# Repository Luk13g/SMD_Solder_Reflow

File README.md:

# SMD_Solder_Reflow
Soldering system for SMD electronic components on PCBs, adapted in a domestic electric oven

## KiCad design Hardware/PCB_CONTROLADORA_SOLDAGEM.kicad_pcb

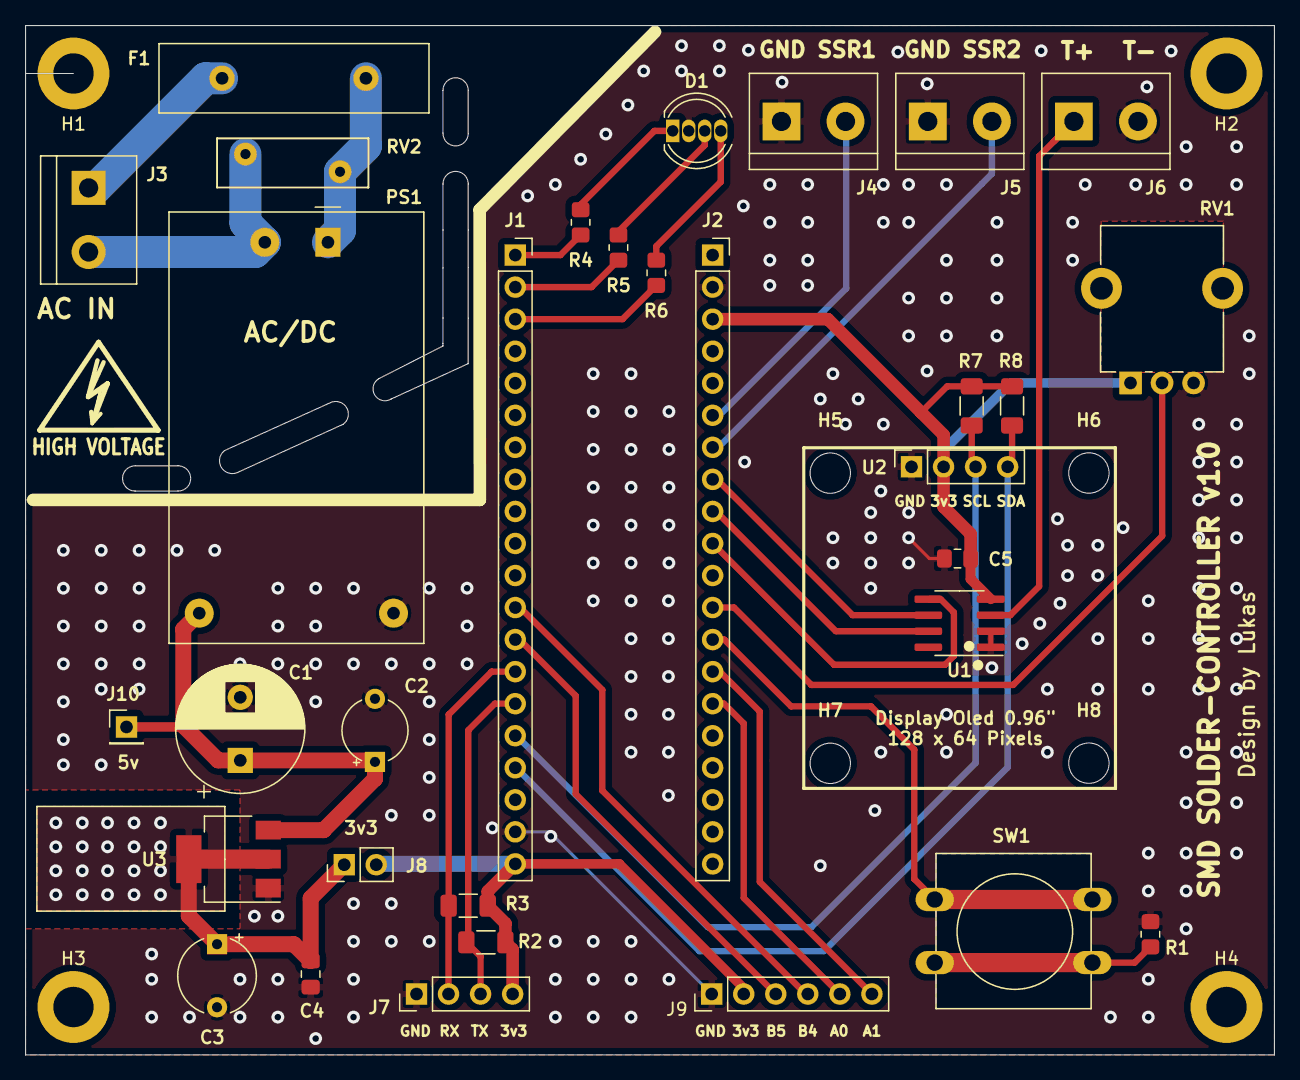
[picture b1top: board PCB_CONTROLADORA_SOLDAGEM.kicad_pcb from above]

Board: 2 copper layers, 99.0 x 81.6 mm, 40 parts (0 on the bottom side), 30 nets.

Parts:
C1: 1000uF; CP_Radial_D10.0mm_P5.00mm
C2: 10uF; CP_Radial_Tantal_D5.0mm_P5.00mm
C3: 22uF; CP_Radial_Tantal_D6.0mm_P5.00mm
C4, C5: 100nF; C_0805_2012Metric_Pad1.18x1.45mm_HandSolder
D1: LED_RCGB; LED_D5.0mm-4_RGB
F1: Fuse; Fuse_Littelfuse-LVR125
H1, H2, H3, H4: MountingHole; MountingHole_3.2mm_M3_ISO7380_Pad
H5, H6, H7, H8: MountingHole; MountingHole_3.2mm_M3
J1, J2: Conn_01x20; PinSocket_1x20_P2.54mm_Vertical
J3: IN_AC; TerminalBlock_bornier-2_P5.08mm
J4: SSR1; TerminalBlock_bornier-2_P5.08mm
J5: SSR2; TerminalBlock_bornier-2_P5.08mm
J6: +THERMO-; TerminalBlock_bornier-2_P5.08mm
J7: Conn_01x04; PinHeader_1x04_P2.54mm_Vertical
J8: Conn_01x02; PinHeader_1x02_P2.54mm_Vertical
J9: Conn_01x06; PinHeader_1x06_P2.54mm_Vertical
J10: Conn_01x01; PinHeader_1x01_P2.54mm_Vertical
PS1: HLK-PM01; Converter_ACDC_HiLink_HLK-PMxx
R1: 5k1; R_0805_2012Metric_Pad1.20x1.40mm_HandSolder
R2, R3, R7, R8: 4k7; R_1206_3216Metric_Pad1.30x1.75mm_HandSolder
R4, R5, R6: R; R_0805_2012Metric_Pad1.20x1.40mm_HandSolder
RV1: R_POT; Potentiometer_Alpha_RD901F-40-00D_Single_Vertical_CircularH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
RV2: S10K250 (250V); RV_Disc_D12mm_W3.9mm_P7.5mm
SW1: SW_Push; SW_PUSH-12mm
U1: MAX6675; SOIC-8_3.9x4.9mm_P1.27mm
U2: OLED; PinSocket_1x04_P2.54mm_Vertical
U3: LM1117-3.3; SOT-223-3_TabPin2

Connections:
+3V3: C5.2, J1.20, J2.3, J7.4, J8.2, J9.2, R2.2, R3.1, R7.1, R8.1, RV1.1, U1.4, U2.2
+5V: C1.1, C2.1, J10.1, PS1.4, U3.3
/I2C1_SCL: J1.16, R7.2, U2.3
/I2C1_SDA: J1.17, R8.2, U2.4
/PA3: J2.12, RV1.2
/SPI1_CS: J2.8, U1.6
/SPI1_MISO: J2.9, U1.7
/SPI1_SCK: J2.10, U1.5
GND: C1.2, C2.2, C3.2, C4.2, C5.1, D1.2, J1.19, J2.2, J4.1, J5.1, J6.2, J7.1, J9.1, PS1.3, R1.1, RV1.3, U1.1, U1.2, U2.1, U3.1
unnamed: C3.1, C4.1, J8.1, U3.2
unnamed: D1.1, R4.1
unnamed: D1.3, R5.2
unnamed: D1.4, R6.2
unnamed: F1.1, PS1.1, RV2.1
unnamed: F1.2, J3.1
unnamed: J1.1, R4.2
unnamed: J1.2, R5.1
unnamed: J1.3, R6.1
unnamed: J1.12, J9.4
unnamed: J1.13, J9.3
unnamed: J1.14, J7.2, R3.2
unnamed: J1.15, J7.3, R2.1
unnamed: J2.6, J4.2
unnamed: J2.7, J5.2
unnamed: J2.13, SW1.1
unnamed: J2.14, J9.6
unnamed: J2.15, J9.5
unnamed: J3.2, PS1.2, RV2.2
unnamed: J6.1, U1.3
unnamed: R1.2, SW1.2

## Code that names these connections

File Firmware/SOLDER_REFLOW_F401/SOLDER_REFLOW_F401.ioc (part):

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Mcu.Name=STM32F401C(B-C)Ux
Mcu.Package=UFQFPN48
Mcu.UserName=STM32F401CCUx
PA13.Mode=Serial_Wire
PA13.Signal=SYS_JTMS-SWDIO
PA14.Mode=Serial_Wire
PA14.Signal=SYS_JTCK-SWCLK
PA2.GPIOParameters=GPIO_PuPd,GPIO_Label,GPIO_ModeDefaultEXTI
PA2.GPIO_Label=BUTTON
PA2.GPIO_ModeDefaultEXTI=GPIO_MODE_IT_FALLING
PA2.GPIO_PuPd=GPIO_PULLUP
PA2.Signal=GPXTI2
PA5.Mode=RX_Only_Simplex_Unidirect_Master
PA5.Signal=SPI1_SCK
PA6.Mode=RX_Only_Simplex_Unidirect_Master
PA6.Signal=SPI1_MISO
PA7.GPIOParameters=GPIO_Label
PA7.GPIO_Label=SPI1_CS
PA7.Signal=GPIO_Output
PB1.GPIOParameters=GPIO_Label
PB1.GPIO_Label=SSR1
PB1.Signal=S_TIM3_CH4
PB12.GPIOParameters=GPIO_Label
PB12.GPIO_Label=LED_RED
PB12.Signal=GPIO_Output
PB13.GPIOParameters=GPIO_Label
PB13.GPIO_Label=LED_GREEN
PB13.Signal=GPIO_Output
PB14.GPIOParameters=GPIO_Label
PB14.GPIO_Label=LED_BLUE
PB14.Signal=GPIO_Output
PB6.Mode=Asynchronous
PB6.Signal=USART1_TX
PB7.Mode=Asynchronous
PB7.Signal=USART1_RX
PB8.Mode=I2C
PB8.Signal=I2C1_SCL
PB9.Mode=I2C
PB9.Signal=I2C1_SDA
PC13-ANTI_TAMP.GPIOParameters=PinState,GPIO_Label
PC13-ANTI_TAMP.GPIO_Label=LED_USER
PC13-ANTI_TAMP.PinState=GPIO_PIN_SET
PC13-ANTI_TAMP.Signal=GPIO_Output
PC14-OSC32_IN.Mode=LSE-External-Oscillator
PC14-OSC32_IN.Signal=RCC_OSC32_IN
PC15-OSC32_OUT.Mode=LSE-External-Oscillator
PC15-OSC32_OUT.Signal=RCC_OSC32_OUT
PH0\ -\ OSC_IN.Mode=HSE-External-Oscillator
PH0\ -\ OSC_IN.Signal=RCC_OSC_IN
PH1\ -\ OSC_OUT.Mode=HSE-External-Oscillator
PH1\ -\ OSC_OUT.Signal=RCC_OSC_OUT
RCC.HSE_VALUE=25000000
RCC.SYSCLKFreq_VALUE=84000000
RCC.SYSCLKSource=RCC_SYSCLKSOURCE_PLLCLK
board=custom

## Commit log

2022-12-28 scilab code, for monitoring the oven's internal temperature interface
2022-12-28 PCB hardware for reading and controlling the oven's internal temperature
2022-12-28 I modified the folder where the hardware is located
2022-12-28 3D case for fixing electronics
2022-12-28 soldering oven control firmware
2022-12-28 full system images
